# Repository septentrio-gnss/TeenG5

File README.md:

# TeenG5

p

|TeenG5| Carrier board for Teensy 4.1|
|------|-------|
|Author|  [laekaz](https://github.com/laekaz)|
|Maintainer| [Septentrio gnss github user](githubuser@septentrio.com)|
|external website| https://github.com/septentrio-gnss/TeenG5  |
|License| [CC BY-SA 4.0](https://creativecommons.org/licenses/by-sa/4.0/) and [open source](https://www.oshwa.org/definition/) |

## Table of Content

* [What is TeenG5](#what-is-teeng5)
    * [What is the Teensy 4.1?](#what-is-the-teensy-41)
    * [What is a Carrier Board for Teensy 4.1?](#what-is-a-carrier-board-for-teensy-41)
    * [Produce Yourself?](#produce-yourself)
            * [Do I Need to Source Special Components for Producing This Board?](#do-i-need-to-source-special-components-for-producing-this-board)
    * [What is a mosaic-G5 Module?](#what-is-a-mosaic-g5-module)
        * [Other mosaic-G5 Versions](#other-mosaic-g5-versions)
    * [Who is Septentrio?](#who-is-septentrio)
    * [Deliverables](#deliverables)
    * [Is the Project Open-Source?](#is-the-project-open-source)
* [Disclaimer](#disclaimer)
* [Documentation Sections](#documentation-sections)

## What is TeenG5
This is a compact carrier board that brings high precision GNSS (GPS) which integrates mosaic-G5 Septentrio's GNSS module with basic communications, allowing the system to receive signals from multiple GNSS constellations, such as GPS, Galileo, GLONASS, and BeiDo. The goal of the design is to simplify hardware prototyping and integration of the mosaic-G5 by taking advantage of the [Teensy 4.1's](https://www.pjrc.com/store/teensy41.html) high-performance microcontroller, extensive peripheral interfaces, and Arduino-compatible development ecosystem. This makes TeenG5 well suited for embedded applications such as robotics, autonomous vehicles, UAVs, precision agriculture, surveying, timing, and other systems that require low-latency GNSS processing without relying on an external computer.
 
The board can also operate as a standalone device when powered through its USB connector.

### What is the Teensy 4.1?
The [Teensy 4.1](https://www.pjrc.com/store/teensy41.html) is a compact, high-performance microcontroller development board based on the NXP i.MX RT1062 ARM Cortex-M7 processor running at 600 MHz. It offers 1 MB of RAM, 8 MB of onboard flash memory, a microSD card slot, USB host and device capabilities, Ethernet, and a wide range of digital, analog, and communication interfaces (UART, SPI, I²C, and CAN). Compatible with the Arduino IDE through Teensyduino software, it is well suited for robotics, real-time control,embedded systems, audio processing, data acquisition, and other performance-critical applications.

### What is a carrier board for Teensy 4.1?
A carrier board is a board that hosts a removable Teensy 4.1. The Teensy plugs into the board through two 24-pin headers and can be removed or replaced, while the carrier board integrates the Septentrio mosaic-G5 GNSS receiver, power management, and communication interfaces into a single embedded platform.

### Produce yourself?
You can use the design files, Bill of Materials from this project and contact your manufacturing company for production. In this project we used [JLCPCB](https://jlcpcb.com/) for producing the PCB and assembling it. We used JLCPCB because of its competitive pricing and component availability.

##### Do I need to source special components for producing this board?

Yes, Some components are not available through JLCPCB's standard parts library and must be supplied separately. however, if you are assembling the PCB by yourself, all components are available on DigiKey and clearly listed in the project's Bill of Materials. The mosaic GNSS module can be obtained from Digikey or directly from Septentrio. For larger production volumes, we recommend contacting the Septentrio sales team directly at [Septentrio Contact Page](https://www.septentrio.com/en/contact/ask-question)

### What is a mosaic-G5 module?
The mosaic-G5 is a compact GNSS receiver from Septentrio, engineered for high reliability and precise positioning. It integrates the latest multi-band, multi-constellation GNSS technology, providing accurate positions while minimizing power consumption. The receiver can access signals from all major GNSS constellations, including GPS, Galileo, GLONASS, and BeiDou.

#### Other mosaic-G5 versions
Different versions of the mosaic-G5 are available to suit various applications, as summarized below:

| Features     | [mosaic-G5 P1](https://www.septentrio.com/en/products/gnss-receivers/gnss-receiver-modules/mosaic-g5-p1) | [mosaic-G5 P3](https://www.septentrio.com/en/products/gnss-receivers/gnss-receiver-modules/mosaic-G5-P3) | [mosaic-G5 P3H](https://www.septentrio.com/en/products/gnss-receivers/gnss-receiver-modules/mosaic-G5-P3H) |[mosaic-G5 P6](https://www.septentrio.com/en/products/gnss-receivers/gnss-receiver-modules/mosaic-G5-P6) | [mosaic-G5 P8](https://www.septentrio.com/en/products/gnss-receivers/gnss-receiver-modules/mosaic-g5-p8) |
|--------------|--------------|--------------|---------------|---------------|---------------|
| Functionality|High-precision positioning   |High-precision positioning |Positioning + Heading|Positioning + Heading | Positioning + Heading|
| Use case     |Robotics (e.g robotic mowers), GIS devices |UAV, Commercial mowers, Industrial Robotics, Survey, Marine navigation | Marine navigation, Machine control, Autonomous vehicles,  Survey | Autonomous vehicles, Marine navigation, Machine control, Survey | High-end autonomous systems, Robotics, Marine navigation, Survey, Machine control |          
| GNSS bands   | Triple-band  | Quad-band    | Quad-band     |Quad-band |Quad-band  |
| RTK support  | Yes          | Yes          | Yes           |Yes       |Yes        |
| Dual antenna |    No        |  No          | Yes           |Yes       |Yes        |
| Heading      |     NO       |   No         | Yes           |Yes       |Yes        |

### Who is Septentrio?

Septentrio is a leading company that designs, manufactures and sells high precision and multi-frequency GPS/GNSS receivers for demanding applications. Septentrio products are used in different industries including automotive, marine, construction, rail, machine control, logistics, precision agriculture, geographic information systems (GIS), Unmanned aerial vehicles (UAVs), surveying, mapping and scientific development. Septentrio’s receivers constantly deliver accurate and precise GNSS positioning scalable to centimetre-level and designed to perform perfectly in challenging environments. 

Septentrio's technology offers high accuracy and reliability thanks to advanced GNSS signal-processing algorithms as well as [Advanced interference Monitoring and Mitigation (AIM+)](https://www.septentrio.com/en/learn-more/advanced-positioning-technology/aim-anti-jamming-protection) This protects your application against jamming (RF interference) and spoofing (malicious attacks).

For more information about Septentrio products go to [**https://www.septentrio.com/**](https://web.septentrio.com/GH-SSN-home).

### Deliverables
This project provides the following deliverables for system integrators and hardware designers developing solutions based on Septentrio's mosaic-G5 modules.

|Files         |Description   |
|--------------|--------------|
|  [G5_Teensy.kicad_pro](./Kicad/TeenG5/G5_Teensy.kicad_pro)   |KiCad project |
| [G5_Teensy.kicad_pcb](./Kicad/TeenG5/G5_Teensy.kicad_pcb) | KiCad layout |
|  [G5_Teensy.kicad_sch](./Kicad/TeenG5/G5_Teensy.kicad_sch)  |KiCad schematic |
| [TeenG5 3D.step](./Kicad/TeenG5%203D/teenG5%203D.step)   | TeenG5 3D|
| [mosaic-G5.STEP](./Kicad/mosaci-G5/mosaic-G5.STEP)  |mosaic-G5 3D |
| [LGA54_MOSAIC-MINI_SEP.kicad_mod](./Kicad/mosaci-G5/LGA54_MOSAIC-MINI_SEP.kicad_mod)  |mosaic-G5 footprint |
|  [BOM](./Kicad/BOM.xlsx) | TeenG5 Bill of Materials |
### Is the project open-source?
Yes, We made this open source so you can tinker, adapt, and create. If you are building your own robotics project, a spin-off device, or integrating GNSS into a larger system, this is a great starting point.

Open source here means:
* All files fully editable
* Freedom to modify, remix, and innovate
* You can sell your version. No -NC limitations
* May require attribution
* Build on our work, push it further, and even make money doing it

More info about licensing can be found here: [CC BY-SA 4.0](https://creativecommons.org/licenses/by-sa/4.0/) and [open source](https://www.oshwa.org/definition/)

## Disclaimer
This project is **offered as-is**. The main interfaces have been tested, but the design has not been fully checked or approved by the author or Septentrio. You are responsible for how you use it in your own projects. For guidance on working with Septentrio’s GNSS mosaic-G5 modules, we suggest reaching out to Septentrio directly.

Support website: https://www.septentrio.com/en/support
## Documentation Sections

This project provides two main documentation sections:

- **[TeenG5 User Documentation](./TeenG5%20User%20Documentation.md)**  
  Contains information for users on how to install, configure, and use the TeenG5.

- **[TeenG5 Design Documentation](./TeenG5%20Design%20Documentation.md)**  
  Intended for hardware designers who want to understand, customize, or modify the reference design of the TeenG5.

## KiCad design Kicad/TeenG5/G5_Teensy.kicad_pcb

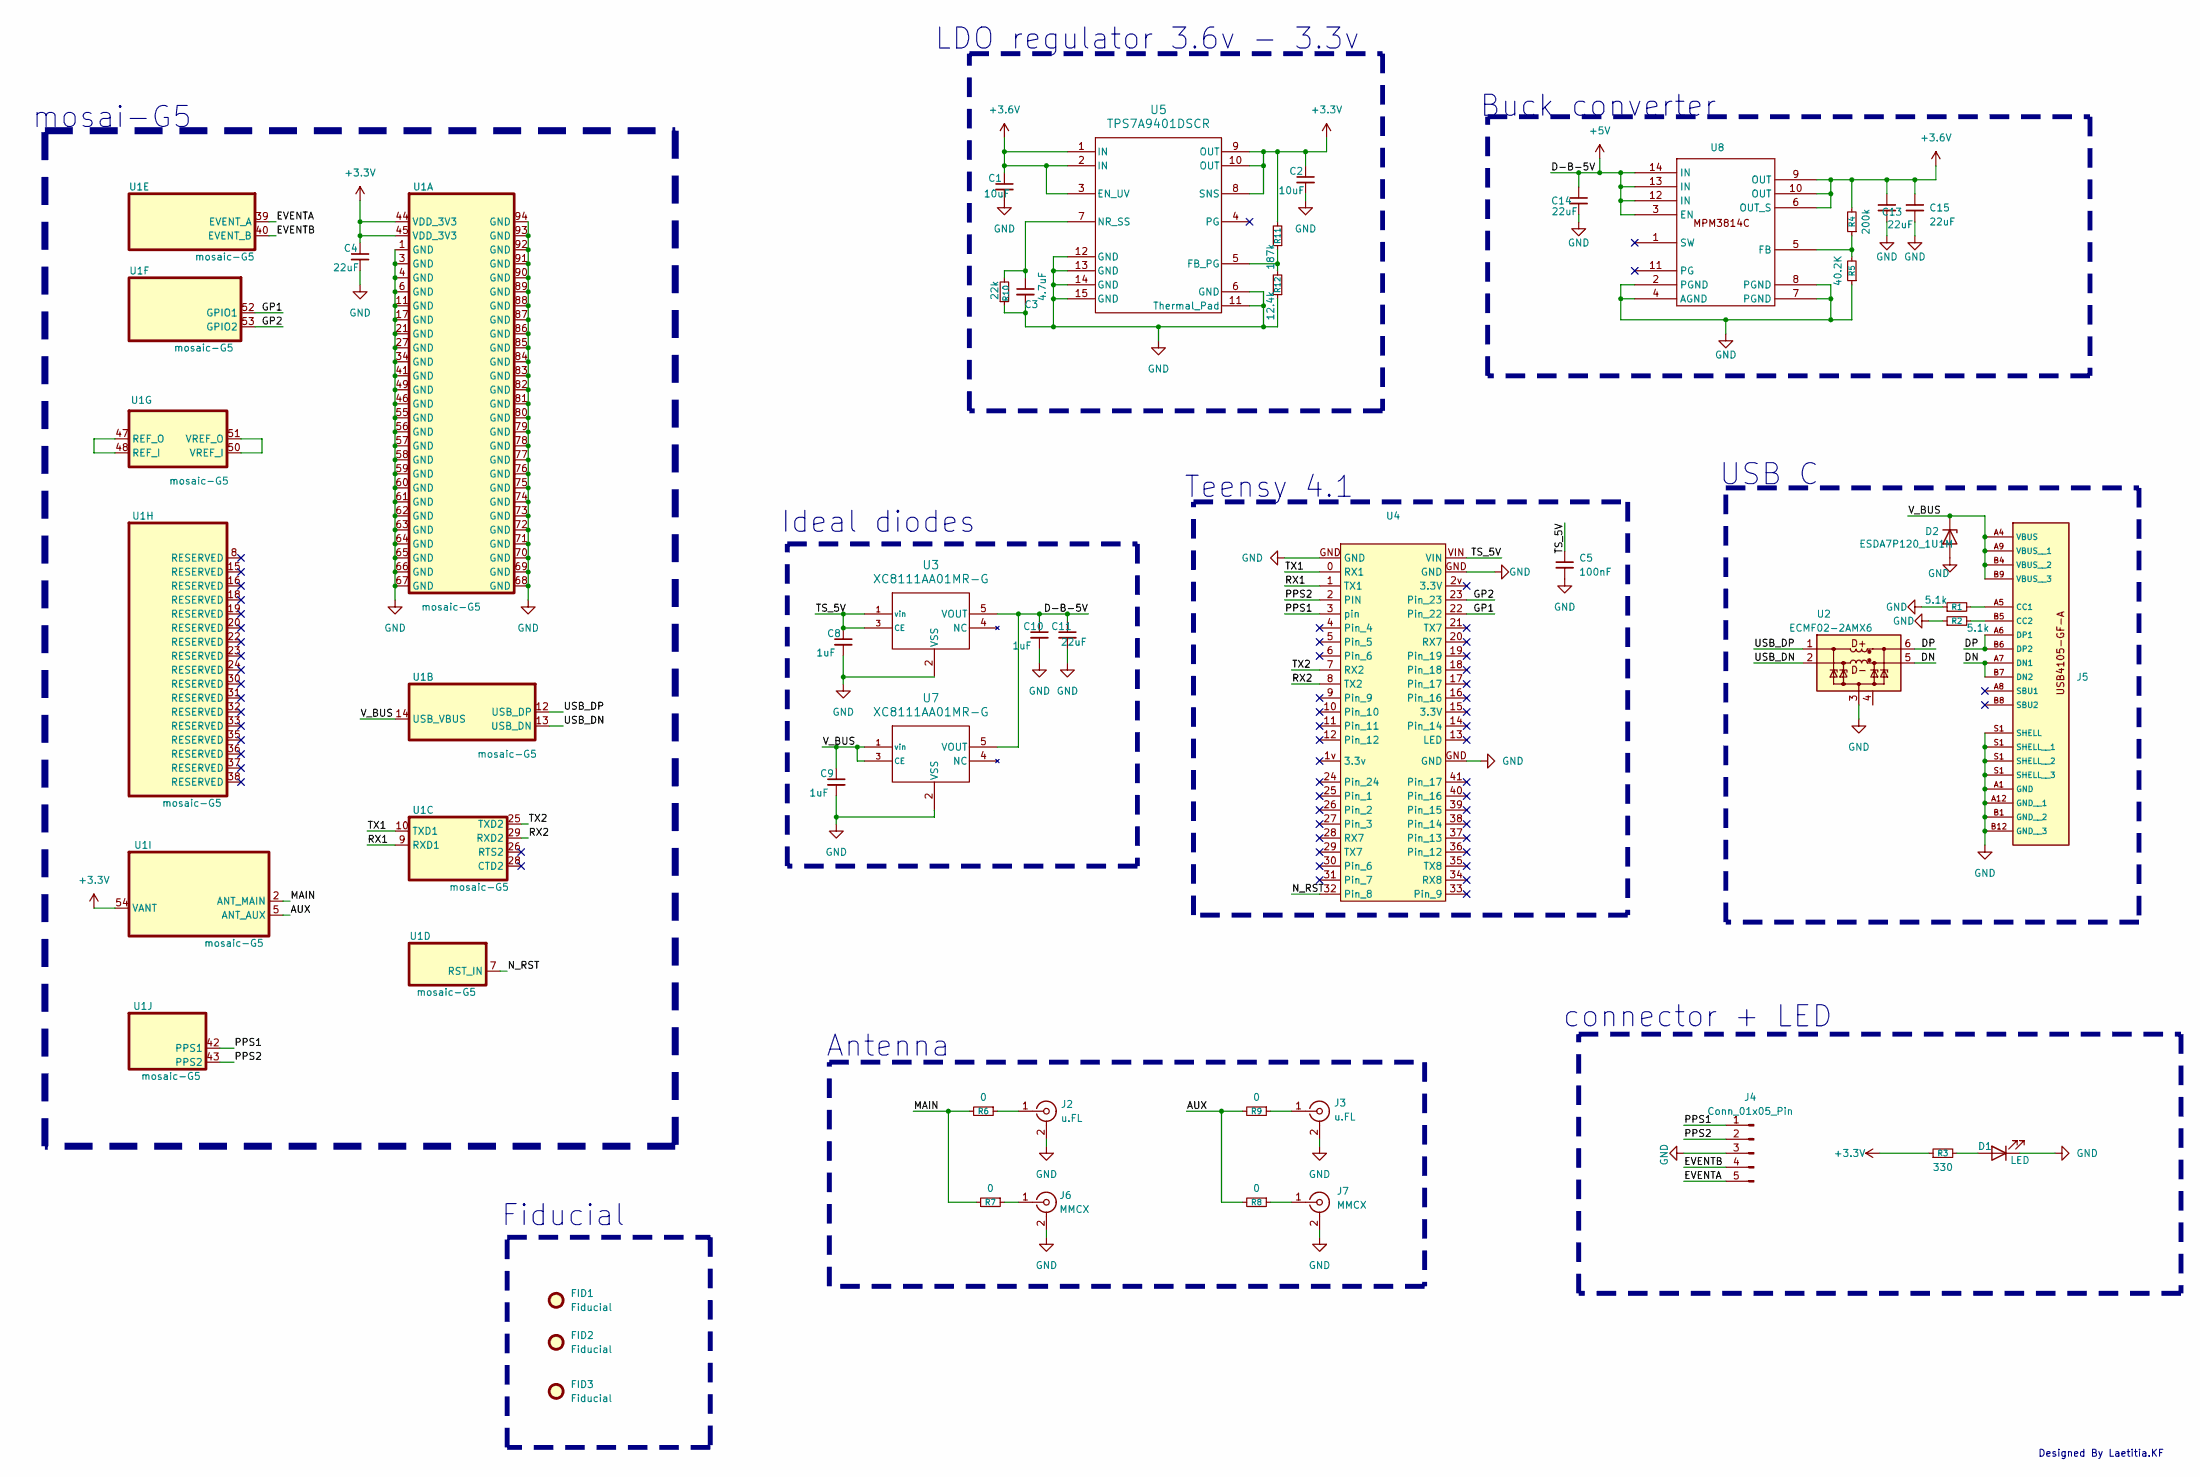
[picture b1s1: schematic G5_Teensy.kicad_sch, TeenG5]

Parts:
C1, C2: 10uF; C_0603_1608Metric
C3: 4.7uF; C_0603_1608Metric
C4: 22uF; C_0603_1608Metric
C5: 100nF; C_0603_1608Metric
C8, C9, C10: 1uF; C_0603_1608Metric
C11, C13, C14, C15: 22uF; C_0805_2012Metric
D1: LED; LED_0603_1608Metric
D2: ESDA7P120_1U1M; DIODE_ESDA7P120-1U1M_STM
FID1, FID2, FID3: Fiducial; Fiducial_1mm_Mask2mm
J2, J3: u.FL; U.FL_Hirose_U.FL-R-SMT-1_Vertical
J4: Conn_01x05_Pin; PinHeader_1x05_P1.27mm_Vertical
J5: USB_C_Receptacle_GCT_USB4105-xx-A_16P_TopMnt_Horizontal
J6, J7: MMCX; CONMMCX002-SMD
R1: 5.1k; C_0402_1005Metric
R2: 5.1k; R_0402_1005Metric
R3: 330; R_0603_1608Metric
R4: 200k; C_0402_1005Metric
R5: 40.2K; R_0402_1005Metric
R6, R7, R8, R9: 0; R_0402_1005Metric
R10: 22k; R_0603_1608Metric
R11: 187k; R_0603_1608Metric
R12: 12.4k; R_0603_1608Metric
U1: mosaic-G5; LGA54_MOSAIC-MINI_SEP
U2: ECMF02-2AMX6; ST_UQFN-6L_1.5x1.7mm_P0.5mm
U3, U7: XC8111AA01MR-G; SOT-25_TOR
U4: Untitled_1
U5: TPS7A9401DSCR; DSC0010J-MFG
U8: ECLGA-14_MPM3814C_MNP

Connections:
+3.3V: C2.1, C4.1, R3.1, R11.2, U1.44 (VDD_3V3), U1.45 (VDD_3V3), U1.54 (VANT), U5.8 (SNS), U5.9 (OUT), U5.10 (OUT)
+3.6V: C1.1, C13.1, C15.1, R4.2, U5.1 (IN), U5.2 (IN), U5.3 (EN_UV), U8.6 (OUT_S), U8.9 (OUT), U8.10 (OUT)
+5V: C10.1, C11.1, C14.1, U3.5 (VOUT), U7.5 (VOUT), U8.3 (EN), U8.12 (IN), U8.13 (IN), U8.14 (IN)
/AUX: R8.2, R9.2, U1.5 (ANT_AUX)
/DN: J5.A7 (DN1), J5.B7 (DN2), U2.5 (D-_out)
/DP: J5.A6 (DP1), J5.B6 (DP2), U2.6 (D+_out)
/EVENTA: J4.5, U1.39 (EVENT_A)
/EVENTB: J4.4, U1.40 (EVENT_B)
/GP1: U1.52 (GPIO1), U4.22
/GP2: U1.53 (GPIO2), U4.23
/MAIN: R6.2, R7.2, U1.2 (ANT_MAIN)
/N_RST: U1.7 (RST_IN), U4.32 (Pin_8)
/PPS1: J4.1, U1.42 (PPS1), U4.3 (pin)
/PPS2: J4.2, U1.43 (PPS2), U4.2 (PIN)
/RX1: U1.9 (RXD1), U4.1 (TX1)
/RX2: U1.29 (RXD2), U4.8 (TX2)
/TS_5V: C5.1, C8.1, U3.1 (vin), U3.3 (CE), U4.VIN
/TX1: U1.10 (TXD1), U4.0 (RX1)
/TX2: U1.25 (TXD2), U4.7 (RX2)
/USB_DN: U1.13 (USB_DN), U2.2 (D-_in)
/USB_DP: U1.12 (USB_DP), U2.1 (D+_in)
/V_BUS: C9.1, D2.1 (K), J5.A4 (VBUS), J5.A9 (VBUS__1), J5.B4 (VBUS__2), J5.B9 (VBUS__3), U1.14 (USB_VBUS), U7.1 (vin), U7.3 (CE)
GND: C1.2, C2.2, C3.2, C4.2, C5.2, C8.2, C9.2, C10.2, C11.2, C13.2, C14.2, C15.2, D1.1 (K), D2.2 (A), J2.2 (Ext), J3.2 (Ext), J4.3, J5.A1 (GND), J5.A12 (GND__1), J5.B1 (GND__2), J5.B12 (GND__3), J5.S1 (SHELL__2), J6.2 (Ext), J7.2 (Ext), R1.1, R2.1, R5.1, R10.1, R12.1, U1.1 (GND), U1.3 (GND), U1.4 (GND), U1.6 (GND), U1.11 (GND), U1.17 (GND), U1.21 (GND), U1.27 (GND), U1.34 (GND), U1.41 (GND), U1.46 (GND), U1.49 (GND), U1.55 (GND), U1.56 (GND), U1.57 (GND), U1.58 (GND), U1.59 (GND), U1.60 (GND), U1.61 (GND), U1.62 (GND), U1.63 (GND), U1.64 (GND), U1.65 (GND), U1.66 (GND), U1.67 (GND), U1.68 (GND), U1.69 (GND), U1.70 (GND), U1.71 (GND), U1.72 (GND), U1.73 (GND), U1.74 (GND), U1.75 (GND), U1.76 (GND), U1.77 (GND), U1.78 (GND), U1.79 (GND), U1.80 (GND), U1.81 (GND), U1.82 (GND), U1.83 (GND), U1.84 (GND), U1.85 (GND), U1.86 (GND), U1.87 (GND), U1.88 (GND), U1.89 (GND), U1.90 (GND), U1.91 (GND), U1.92 (GND), U1.93 (GND), U1.94 (GND), U2.3 (GND), U3.2 (VSS), U4.GND, U5.6 (GND), U5.11 (Thermal_Pad), U5.12 (GND), U5.13 (GND), U5.14 (GND), U5.15 (GND), U7.2 (VSS), U8.2 (PGND), U8.4 (AGND), U8.7 (PGND), U8.8 (PGND)
unnamed: D1.2 (A), R3.2
unnamed: J2.1 (In), R6.1
unnamed: J3.1 (In), R9.1
unnamed: J5.A5 (CC1), R1.2
unnamed: J5.B5 (CC2), R2.2
unnamed: J6.1 (In), R7.1
unnamed: J7.1 (In), R8.1
unnamed: U1.47 (REF_O), U1.48 (REF_I)
unnamed: U1.50 (VREF_I), U1.51 (VREF_O)
unnamed: R11.1, R12.2, U5.5 (FB_PG)
unnamed: C3.1, R10.2, U5.7 (NR_SS)
unnamed: R4.1, R5.2, U8.5 (FB)

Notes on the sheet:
LDO regulator 3.6v - 3.3v
Teensy 4.1
Buck converter
connector + LED
Fiducial
Antenna
Ideal diodes
mosai-G5
USB C
Designed By Laetitia.KF

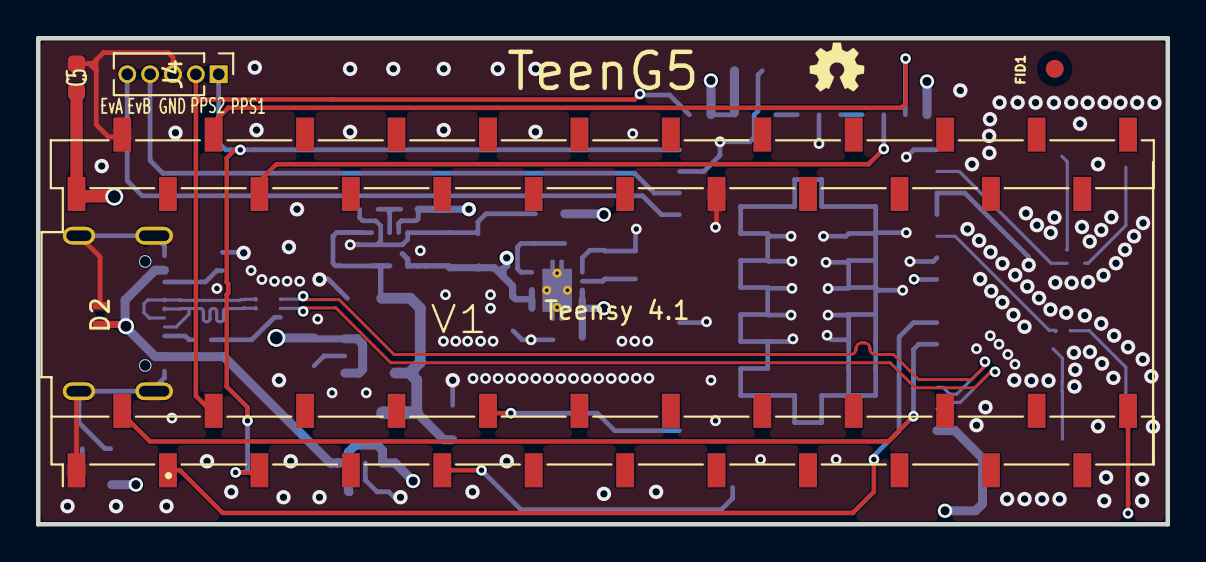
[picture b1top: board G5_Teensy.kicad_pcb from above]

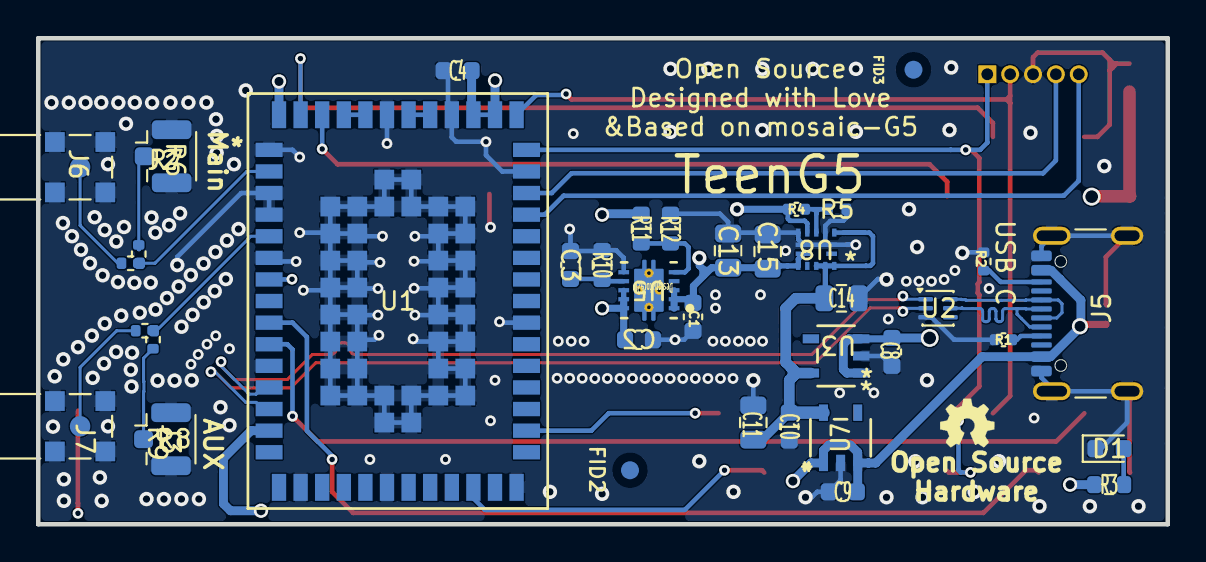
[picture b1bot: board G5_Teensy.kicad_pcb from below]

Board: 4 copper layers, 62.8 x 27.0 mm, 42 parts (37 on the bottom side), 35 nets.

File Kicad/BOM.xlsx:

Designator | Value | Package | JLCPCB Parts | Quantity
C1 | 10uF | C_0603_1608Metric | C22399626 | 1
C2 | 10uF | C_0603_1608Metric | C22399626 | 1
C3 | 4.7uF | C_0603_1608Metric | C1705 | 1
C4 | 22uF | C_0603_1608Metric | C109447 | 1
C5 | 100nF | C_0603_1608Metric | C108079 | 1
C8 | 1uF | C_0603_1608Metric | C106248 | 1
C9 | 1uF | C_0603_1608Metric | C106248 | 1
C10 | 1uF | C_0603_1608Metric | C106248 | 1
C11 | 22uF | C_0805_2012Metric | C23692981 | 1
C13 | 22uF | C_0805_2012Metric | C23692981 | 1
C14 | 22uF | C_0805_2012Metric | C23692981 | 1
C15 | 22uF | C_0805_2012Metric | C23692981 | 1
D1 | LED | LED_0603_1608Metric | C440514 | 1
D2 | ESDA7P120_1U1M | ESD_ESDA7P120-1U1M | C2969802 | 1
J2 | Conn_Coaxial | U.FL_Hirose_U.FL-R-SMT-1_Vertical |  | 1
J3 | Conn_Coaxial | U.FL_Hirose_U.FL-R-SMT-1_Vertical |  | 1
J4 | Conn_01x05_Pin | PinHeader_1x05_P1.27mm_Vertical | C22438102 | 1
J5 | USB4105-GF-A | USB_C_Receptacle_GCT_USB4105-xx-A_16P_TopMnt_Horizontal | C3020560 | 1
J6 | Conn_Coaxial | CONMMCX002-SMD | C22438298 | 1
J7 | Conn_Coaxial | CONMMCX002-SMD | C22438298 | 1
R1 | 5.1k | C_01005_0402Metric | C881131 | 1
R2 | 5.1k | R_01005_0402Metric | C881131 | 1
R3 | 330 ohms | R_0603_1608Metric | C23138 | 1
R4 | 200k | R_01005_0402Metric | C25764 | 1
R5 | 40.2K | R_01005_0402Metric | C100415 | 1
R6 | 0 | R_01005_0402Metric |  | 1
R7 | 0 | R_01005_0402Metric | C60485 | 1
R8 | 0 | R_01005_0402Metric | C60485 | 1
R9 | 0 | R_01005_0402Metric |  | 1
R10 | 22k | R_0603_1608Metric | C881373 | 1
R11 | 187k | R_0603_1608Metric | C22896 | 1
R12 | 12.4k | R_0603_1608Metric | C22865 | 1
U1 | mosaic-G5-P3 | MOSAIC-G3 P3 | C54015208 | 1
U2 | ECMF02-2AMX6 | ST_UQFN-6L_1.5x1.7mm_P0.5mm | C2651144 | 1
U3 | XC8111AA01MR-G | SOT-25_TOR | C3235548 | 1
U7 | XC8111AA01MR-G | SOT-25_TOR | C3235548 | 1
U4 | Teensy | Untitled_1 |  | 1
U5 | TPS7A9401DSCR | DSC0010J-MFG | C5220127 | 1
U8 | MPM3814C | ECLGA-14_MPM3814C_MNP | C6909500 | 1
